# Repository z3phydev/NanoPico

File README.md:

## NanoPico
# What is it?
Its a RP2040 Devboard ment for software apllications. It features 16 MB of flash storage and a Male USB A port
# Why did I make it?
I made it because well nothing similar exists, there are many rp2040 devboards but I just couldnt find one that was as small as posible with a male port and no gpio.
# How to use / setup
Once you recive the PCB download the 16mb.uf2 file. Plug it into your pc while shorting the F Pads. Once your PC recognises it you can stop shorting the pads. Then copy 16mb.uf2 to the drive. The drive should now disappear and reappear as "CircutPython". From here you can edit boot as you wish or do other things with python.

# 3D Model

# PCB (all layers)

# Schematic

# BOM

|Comment            |Designator                                                  |Footprint                        |JLC Part No.|Mft Part No.   |
|-------------------|------------------------------------------------------------|---------------------------------|------------|---------------|
|100nF              |C4, C5, C6, C10, C11, C12, C13, C14, C15, C16, C17, C20, C21|201                              |C49062      |CL03A104KP3NNNC|
|1uF                |C8, C9                                                      |402                              |C14445      |CL05A105KP5NNNC|
|10uF               |C1, C2, C3                                                  |603                              |C19702      |CL10A106KP8NNNC|
|15pF               |C22, C23                                                    |603                              |C1644       |CL10C150JB8NNNC|
|1 kOhm             |R3, R4                                                      |402                              |C11702      |0402WGF1001TCE |
|27 Ohm             |R5, R6                                                      |402                              |C25100      |0402WGF270JTCE |
|47 kOhm            |R7, R8                                                      |402                              |C25563      |0402WGJ0473TCE |
|10 Ohm             |R9                                                          |603                              |C22859      |0603WAF100JT5E |
|Low Voltage Dropout|U3                                                          | SOT-23-5                        |C404027     |TLV75533PDBVR  |GB
|12MHZ Crystal      |Y2                                                          |SMD2520-4P                       |C90603      |Q24FA20H00687  |
|Male USB A         |J2                                                          |USB A Molex 48037-2200 Horizontal|C136453     |480372100      |
|RP2040             |U1                                                          |LQFN-56 (7x7)                    |C2040       |RP2040         |
|16MB Flash Storage |U2                                                          |SOIC-8-208mil                    |C97521      |W25Q128JVSIQ   |

## Total Price if using PCBWAY with assembly should come to around 120 GBP (160 USD)

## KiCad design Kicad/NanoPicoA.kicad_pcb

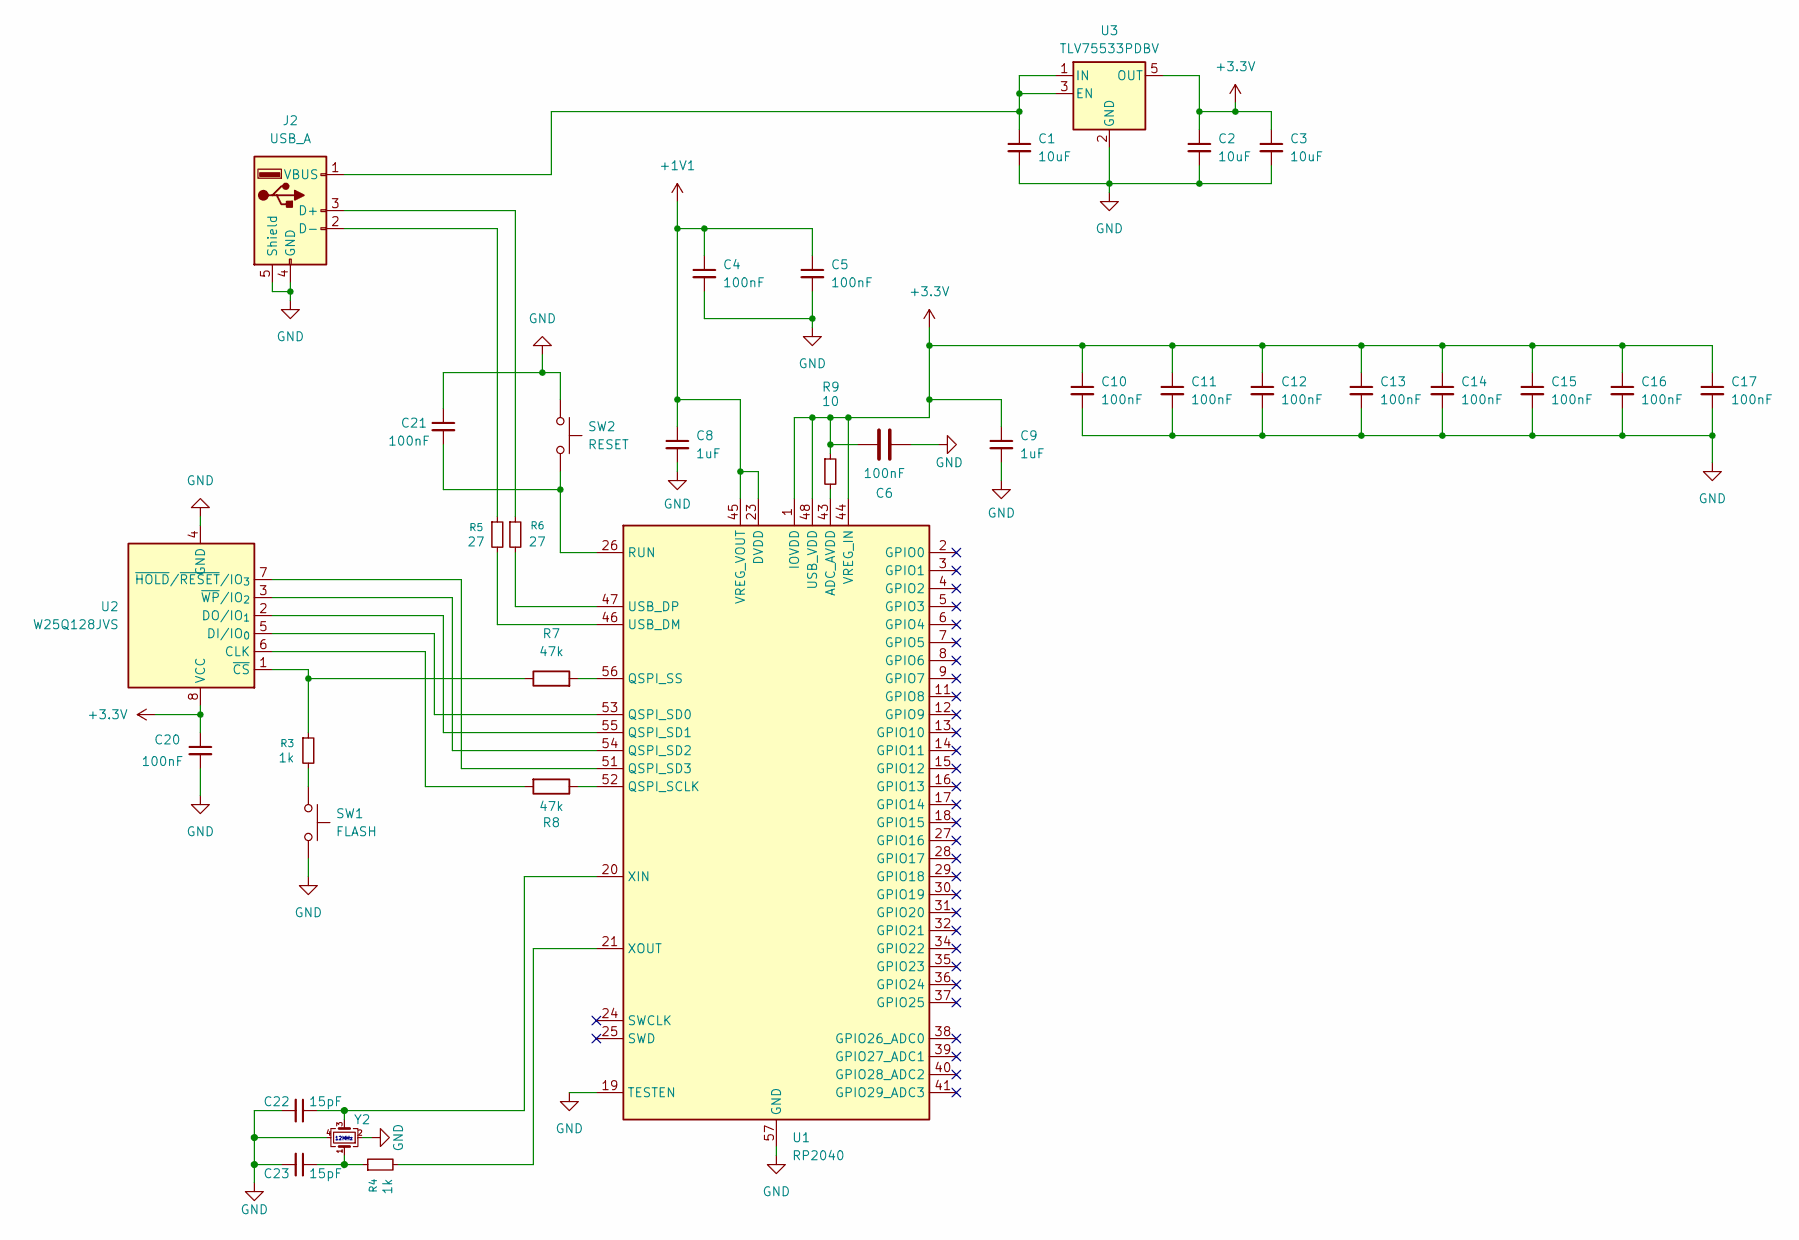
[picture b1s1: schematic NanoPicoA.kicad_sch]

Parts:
C1, C2, C3: 10uF; C_0603_1608Metric_Pad1.08x0.95mm_HandSolder
C4, C5, C6, C10, C11, C12, C13, C14, C15, C16, C17, C20, C21: 100nF; C_0201_0603Metric_Pad0.64x0.40mm_HandSolder
C8, C9: 1uF; C_0402_1005Metric_Pad0.74x0.62mm_HandSolder
C22, C23: 15pF; C_0603_1608Metric
J2: USB_A; USB_A_Molex_48037-2200_Horizontal
R3, R4: 1k; R_0402_1005Metric_Pad0.72x0.64mm_HandSolder
R5, R6: 27; R_0402_1005Metric_Pad0.72x0.64mm_HandSolder
R7, R8: 47k; R_0402_1005Metric_Pad0.72x0.64mm_HandSolder
R9: 10; R_0603_1608Metric_Pad0.98x0.95mm_HandSolder
SW1: FLASH; SWPAD
SW2: RESET; SWPAD
U1: RP2040; QFN-56-1EP_7x7mm_P0.4mm_EP3.2x3.2mm
U2: W25Q128JVS; SOIC-8_5.3x5.3mm_P1.27mm
U3: TLV75533PDBV; SOT-23-5
Y2: XYDBPCNANF-12MHZ; Crystal_SMD_2520-4Pin_2.5x2.0mm; LCSC C521567

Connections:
+1V1: C4.1, C5.1, C8.1, U1.23 (DVDD), U1.45 (VREG_VOUT), U1.50 (DVDD)
+3.3V: C2.1, C3.1, C6.2, C9.1, C10.1, C11.1, C12.1, C13.1, C14.1, C15.1, C16.1, C17.1, C20.1, R9.1, U1.1 (IOVDD), U1.10 (IOVDD), U1.22 (IOVDD), U1.33 (IOVDD), U1.42 (IOVDD), U1.44 (VREG_IN), U1.48 (USB_VDD), U1.49 (IOVDD), U2.8 (VCC), U3.5 (OUT)
GND: C1.2, C2.2, C3.2, C4.2, C5.2, C6.1, C8.2, C9.2, C10.2, C11.2, C12.2, C13.2, C14.2, C15.2, C16.2, C17.2, C20.2, C21.1, C22.2, C23.2, J2.4 (GND), J2.5 (Shield), SW1.2, SW2.1, U1.19 (TESTEN), U1.57 (GND), U2.4 (GND), U3.2 (GND), Y2.2, Y2.4
unnamed: C23.1, R4.1, Y2.1
unnamed: J2.3 (D+), R6.1
unnamed: J2.2 (D-), R5.1
unnamed: C1.1, J2.1 (VBUS), U3.1 (IN), U3.3 (EN)
unnamed: R3.2, SW1.1
unnamed: R9.2, U1.43 (ADC_AVDD)
unnamed: R8.1, U1.52 (QSPI_SCLK)
unnamed: U1.53 (QSPI_SD0), U2.5 (DI/IO_{0})
unnamed: U1.55 (QSPI_SD1), U2.2 (DO/IO_{1})
unnamed: U1.54 (QSPI_SD2), U2.3 (~WP/IO_{2})
unnamed: U1.51 (QSPI_SD3), U2.7 (~HOLD/~RESET/IO_{3})
unnamed: R7.2, U1.56 (QSPI_SS)
unnamed: C21.2, SW2.2, U1.26 (RUN)
unnamed: R5.2, U1.46 (USB_DM)
unnamed: R6.2, U1.47 (USB_DP)
unnamed: C22.1, U1.20 (XIN), Y2.3
unnamed: R4.2, U1.21 (XOUT)
unnamed: R8.2, U2.6 (CLK)
unnamed: R3.1, R7.1, U2.1 (~CS)

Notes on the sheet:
12MHz

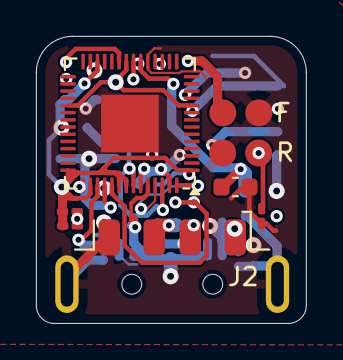
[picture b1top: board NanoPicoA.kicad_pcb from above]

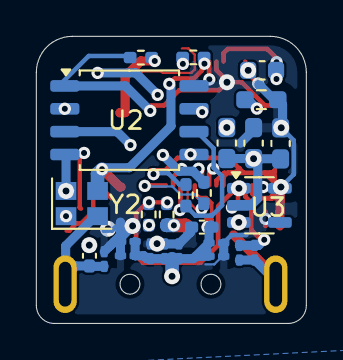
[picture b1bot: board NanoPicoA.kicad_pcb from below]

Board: 4 copper layers, 15.0 x 16.0 mm, 34 parts (26 on the bottom side), 22 nets.

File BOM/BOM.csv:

Comment,Designator,Footprint,JLC Part No.,Mft Part No.
100nF,"C4, C5, C6, C10, C11, C12, C13, C14, C15, C16, C17, C20, C21",201,C49062,CL03A104KP3NNNC
1uF,"C8, C9",402,C14445,CL05A105KP5NNNC
10uF,"C1, C2, C3",603,C19702,CL10A106KP8NNNC
15pF,"C22, C23",603,C1644,CL10C150JB8NNNC
1 kOhm,"R3, R4",402,C11702,0402WGF1001TCE
27 Ohm,"R5, R6",402,C25100,0402WGF270JTCE
47 kOhm,"R7, R8",402,C25563,0402WGJ0473TCE
10 Ohm,R9,603,C22859,0603WAF100JT5E
Low Voltage Dropout,U3,"
SOT-23-5",C404027,TLV75533PDBVR
12MHZ Crystal,Y2,SMD2520-4P,C90603,Q24FA20H00687
Male USB A,J2,USB A Molex 48037-2200 Horizontal,C136453,480372100
RP2040,U1,LQFN-56 (7x7),C2040,RP2040
16MB Flash Storage,U2,SOIC-8-208mil,C97521,W25Q128JVSIQ

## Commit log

2026-02-01 Add placeholder text to fhus file
2026-02-01 Add new file faffdsf in 3D/VRML directory
2026-02-01 Add initial content to BOM/asf
2026-02-01 Create dfsfsf
2026-02-01 Create sdiginos
2026-02-01 Add files via upload
    Note not all parts are present as kicad didnt have a model for them
2026-02-01 Add NanoPico project details to README
    Added detailed information about the NanoPico RP2040 Devboard, including setup instructions, 3D models, PCB layers, schematics, and BOM.
2026-02-01 Add fsaf file with initial content
2026-02-01 Update JOURNAL.md with total time and entry
    Removed auto-generated comment and added total time spent.
2026-02-01 Update total time and add new journal entry
    Updated total time spent and added new entry for repo completion.
2026-02-05 Update total price estimate in README
2026-02-05 PCBWAY BOM
2026-02-05 JLC BOM
